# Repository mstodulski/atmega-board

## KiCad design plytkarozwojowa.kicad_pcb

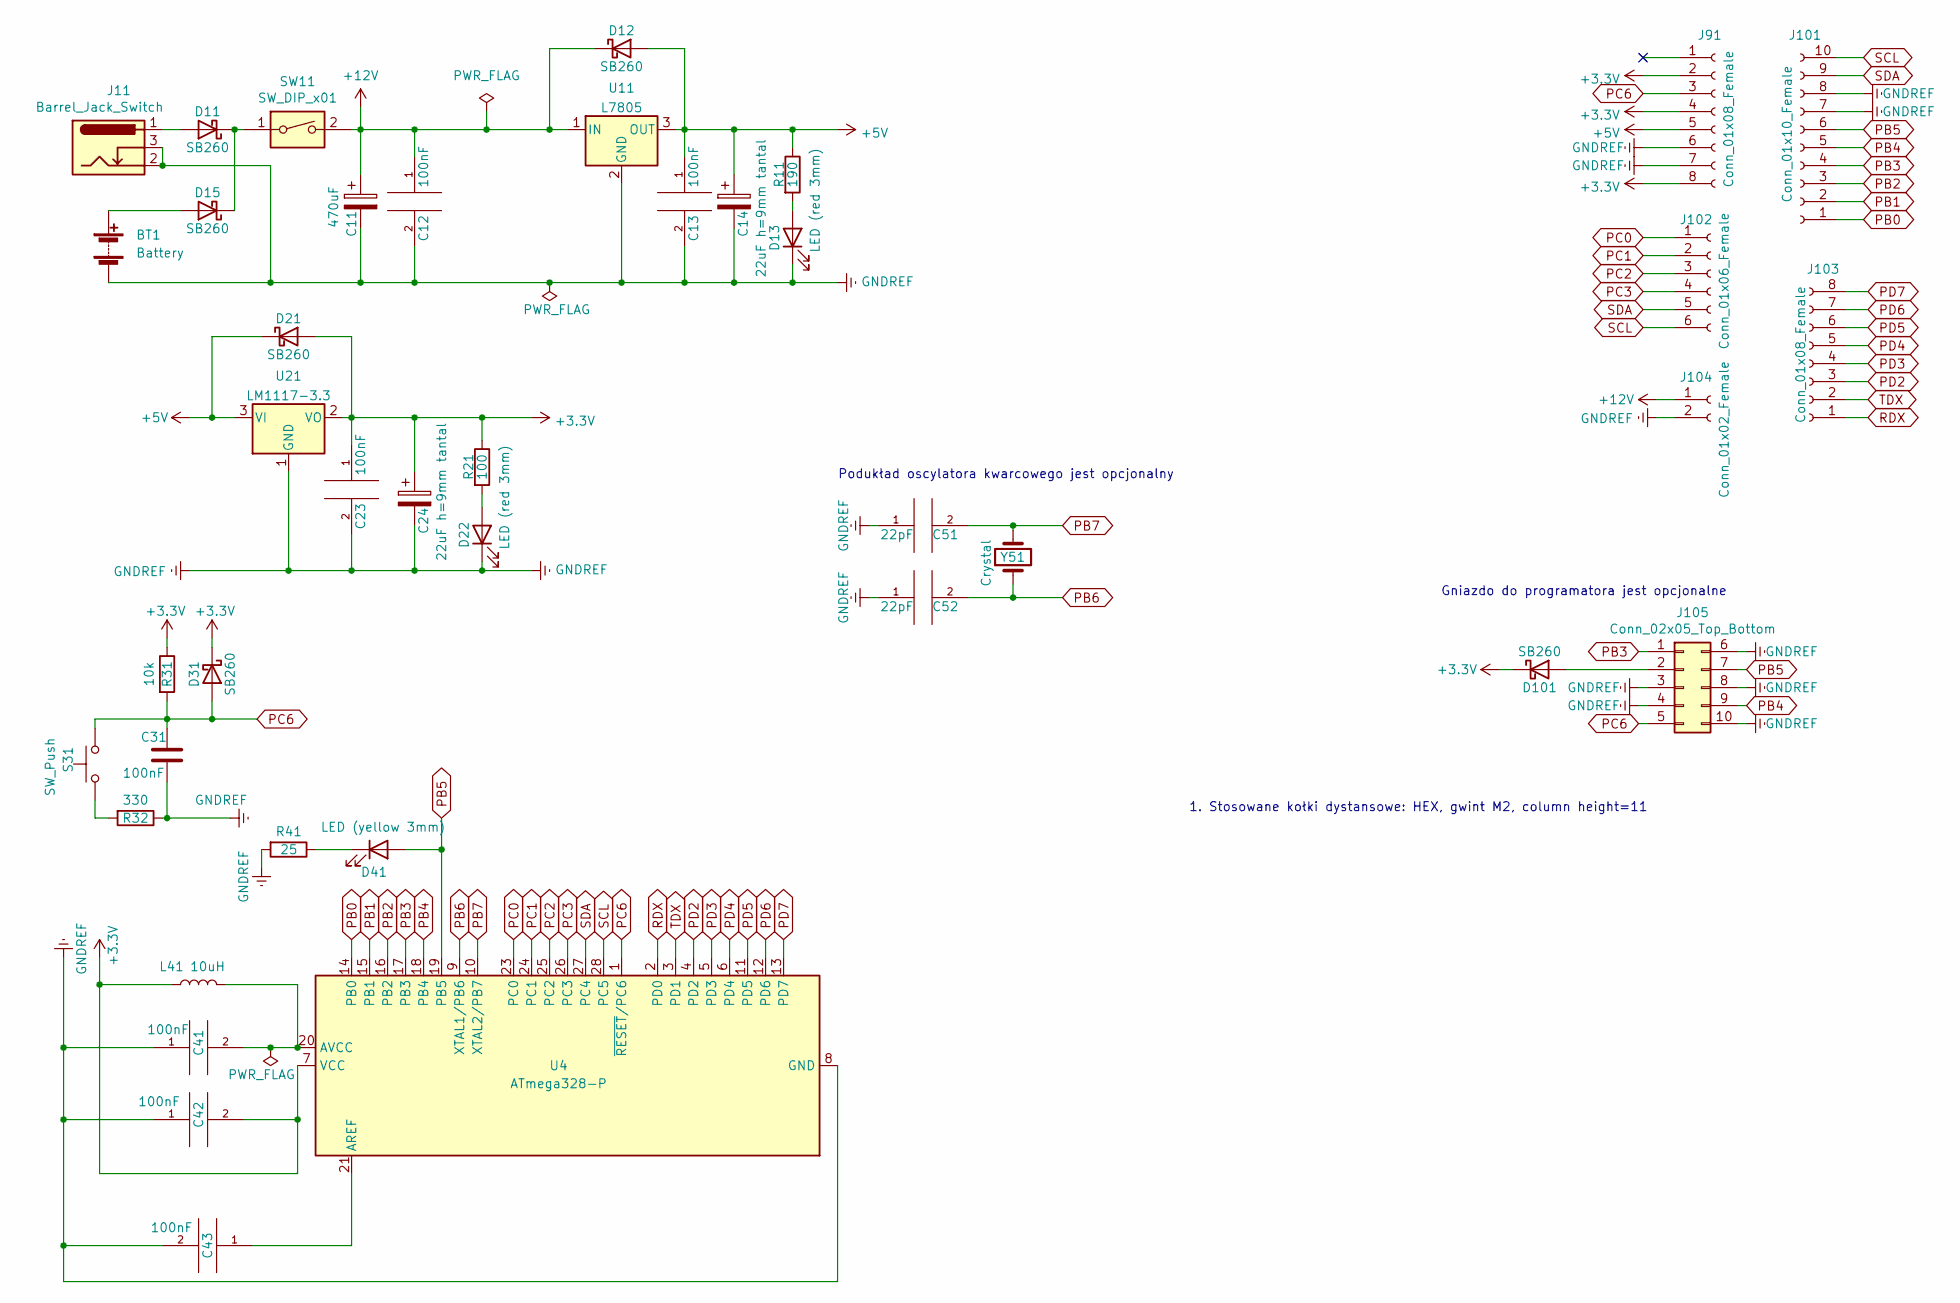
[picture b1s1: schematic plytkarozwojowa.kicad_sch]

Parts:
BT1: Battery; PinSocket_1x02_P2.54mm_Vertical
C11: 470uF; Capacitor_D8_H12_P3.5_Angle
C12, C13, C23, C31, C41, C42, C43: 100nF; C_Disc_D5.0mm_W2.5mm_P2.50mm
C14, C24: 22uF h=9mm tantal; C_Disc_D5.0mm_W2.5mm_P2.50mm
C51, C52: 22pF; C_Disc_D3.0mm_W2.0mm_P2.50mm
D11, D12, D15, D21, D31, D101: SB260; D_A-405_P7.62mm_Horizontal
D13, D22: LED (red 3mm); LED_D3.0mm
D41: LED (yellow 3mm); LED_D3.0mm
J11: Barrel_Jack_Switch; BarrelJack_Wuerth_6941xx301002
J91, J103: Conn_01x08_Female; PinSocket_1x08_P2.54mm_Vertical
J101: Conn_01x10_Female; PinSocket_1x10_P2.54mm_Vertical
J102: Conn_01x06_Female; PinSocket_1x06_P2.54mm_Vertical
J104: Conn_01x02_Female; PinSocket_1x02_P2.54mm_Vertical
J105: Conn_02x05_Top_Bottom; IDC-Header_2x05_P2.54mm_Horizontal
L41: 10uH; L_Axial_L6.6mm_D2.7mm_P10.16mm_Horizontal_Vishay_IM-2
R11: 190; R_Axial_DIN0207_L6.3mm_D2.5mm_P2.54mm_Vertical
R21: 100; R_Axial_DIN0207_L6.3mm_D2.5mm_P2.54mm_Vertical
R31: 10k; R_Axial_DIN0207_L6.3mm_D2.5mm_P2.54mm_Vertical
R32: 330; R_Axial_DIN0207_L6.3mm_D2.5mm_P2.54mm_Vertical
R41: 25; R_Axial_DIN0207_L6.3mm_D2.5mm_P2.54mm_Vertical
S31: SW_Push; SW_Tactile_SPST_Angled_PTS645Vx39-2LFS
SW11: SW_DIP_x01; wlacznik katowy
U4: ATmega328-P; DIP-28_W7.62mm
U11: L7805; TO-220-3_Horizontal_TabDown
U21: LM1117-3.3; TO-220-3_Horizontal_TabUp
Y51: Crystal; Crystal_HC49-4H_Vertical

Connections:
+3.3V: C23.1, C24.1, C42.2, D21.2 (A), D31.1 (K), D101.1 (K), J91.2, J91.4, J91.8, L41.1, R21.1, R31.1, U4.7 (VCC), U21.2 (VO)
+5V: C13.1, C14.1, D12.2 (A), D21.1 (K), J91.5, R11.1, U11.3 (OUT), U21.3 (VI)
+12V: C11.1, C12.1, D12.1 (K), J104.1, SW11.2, U11.1 (IN)
GNDREF: BT1.2 (-), C11.2, C12.2, C13.2, C14.2, C23.2, C24.2, C31.2, C41.1, C42.1, C43.2, C51.1, C52.1, D13.1 (K), D22.1 (K), J11.2, J11.3, J91.6, J91.7, J101.7, J101.8, J104.2, J105.3, J105.4, J105.6, J105.8, J105.10, R32.1, R41.2, U4.8 (GND), U4.22 (GND), U11.2 (GND), U21.1 (GND)
unnamed: BT1.1 (+), D15.2 (A)
unnamed: C41.2, L41.2, U4.20 (AVCC)
unnamed: C43.1, U4.21 (AREF)
unnamed: D11.1 (K), D15.1 (K), SW11.1
unnamed: D11.2 (A), J11.1
unnamed: D13.2 (A), R11.2
unnamed: D22.2 (A), R21.2
unnamed: D41.1 (K), R41.1
unnamed: D101.2 (A), J105.2
unnamed: R32.2, S31.1
PB0: J101.1, U4.14 (PB0)
PB1: J101.2, U4.15 (PB1)
PB2: J101.3, U4.16 (PB2)
PB3: J101.4, J105.1, U4.17 (PB3)
PB4: J101.5, J105.9, U4.18 (PB4)
PB5: D41.2 (A), J101.6, J105.7, U4.19 (PB5)
PB6: C52.2, U4.9 (XTAL1/PB6), Y51.1
PB7: C51.2, U4.10 (XTAL2/PB7), Y51.2
PC0: J102.1, U4.23 (PC0)
PC1: J102.2, U4.24 (PC1)
PC2: J102.3, U4.25 (PC2)
PC3: J102.4, U4.26 (PC3)
PC6: C31.1, D31.2 (A), J91.3, J105.5, R31.2, S31.2, U4.1 (~RESET/PC6)
PD2: J103.3, U4.4 (PD2)
PD3: J103.4, U4.5 (PD3)
PD4: J103.5, U4.6 (PD4)
PD5: J103.6, U4.11 (PD5)
PD6: J103.7, U4.12 (PD6)
PD7: J103.8, U4.13 (PD7)
RDX: J103.1, U4.2 (PD0)
SCL: J101.10, J102.6, U4.28 (PC5)
SDA: J101.9, J102.5, U4.27 (PC4)
TDX: J103.2, U4.3 (PD1)

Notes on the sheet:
1. Stosowane kołki dystansowe: HEX, gwint M2, column height=11
Podukład oscylatora kwarcowego jest opcjonalny
Gniazdo do programatora jest opcjonalne

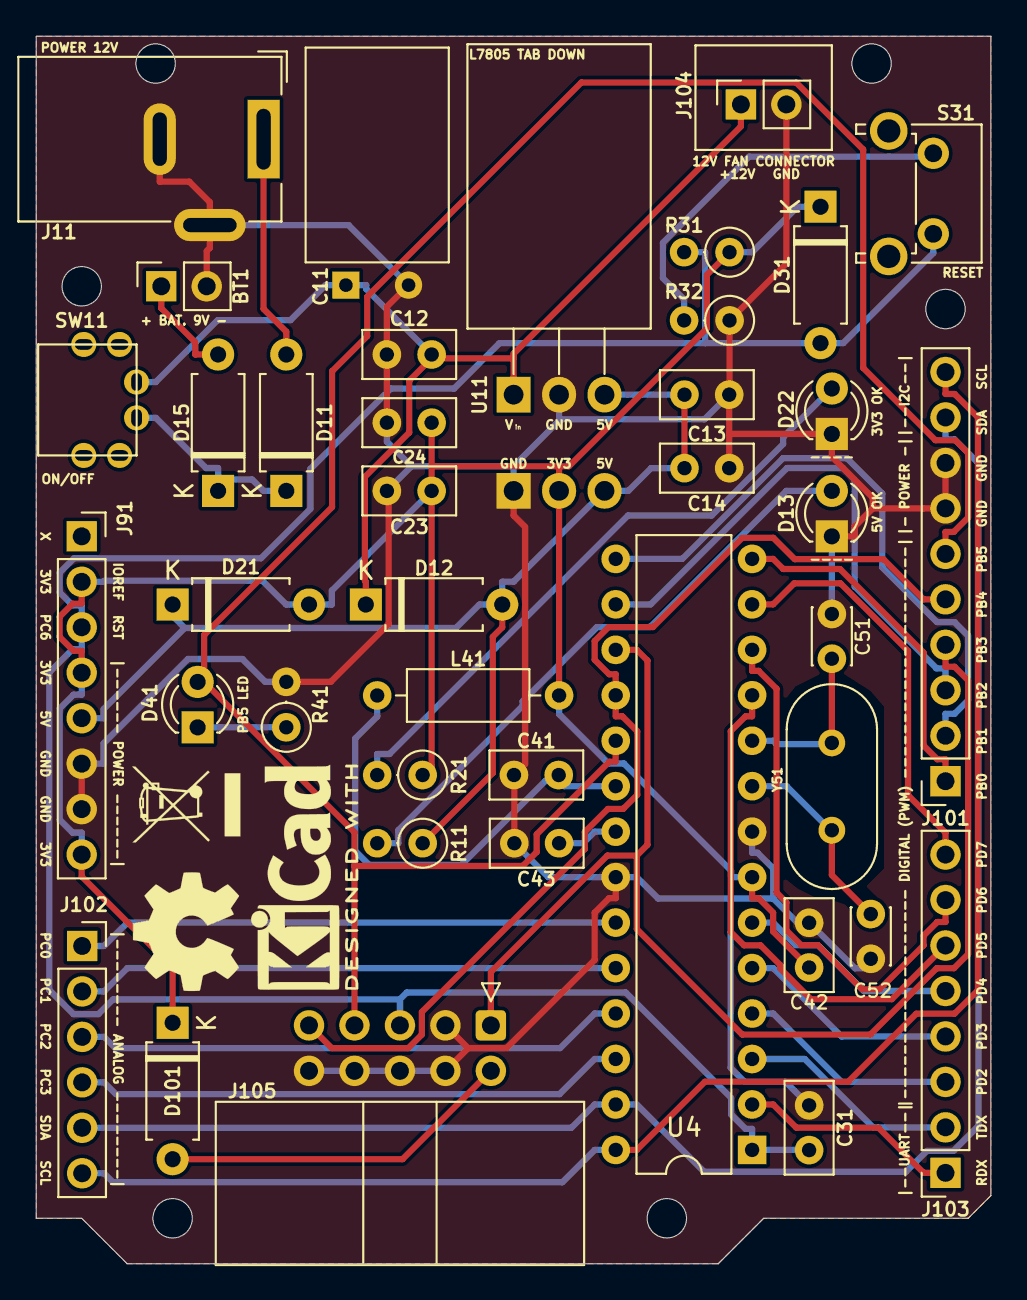
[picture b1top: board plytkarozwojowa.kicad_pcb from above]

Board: 2 copper layers, 53.3 x 68.6 mm, 44 parts (1 on the bottom side), 37 nets.

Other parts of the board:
REFL1: KiCad-Logo2_5mm_SilkScreen
REFL2: OSHW-Symbol_6.7x6mm_SilkScreen
REFL3: WEEE-Logo_4.2x6mm_SilkScreen
